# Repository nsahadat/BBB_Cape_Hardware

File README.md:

# BBB_Cape_Hardware
This cape is used to interface with wheelchair, PC, Smartphones, and Smarthomes

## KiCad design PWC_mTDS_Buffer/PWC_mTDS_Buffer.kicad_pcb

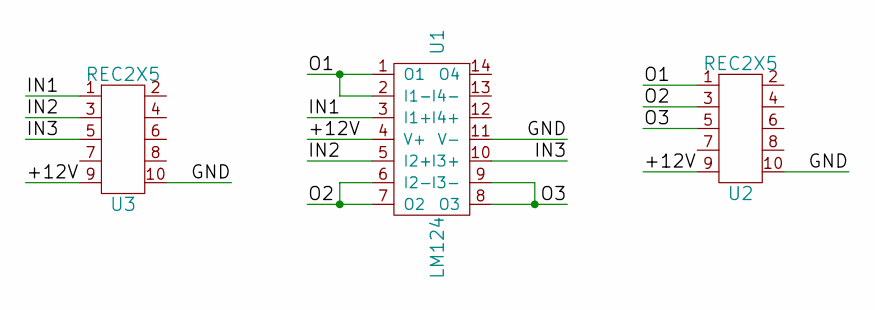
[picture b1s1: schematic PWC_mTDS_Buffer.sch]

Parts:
U1: LM124
U2: REC2X5; REC2X5_254MM
U3: REC2X5; REC2X5_127MM

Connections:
/+12V: U1.4 (V+), U2.9, U3.9
/GND: U1.11 (V-), U2.10, U3.10
/IN1: U1.3 (I1+), U3.1
/IN2: U1.5 (I2+), U3.3
/IN3: U1.10 (I3+), U3.5
/O1: U1.1 (O1), U1.2 (I1-), U2.1
/O2: U1.6 (I2-), U1.7 (O2), U2.3
/O3: U1.8 (O3), U1.9 (I3-), U2.5

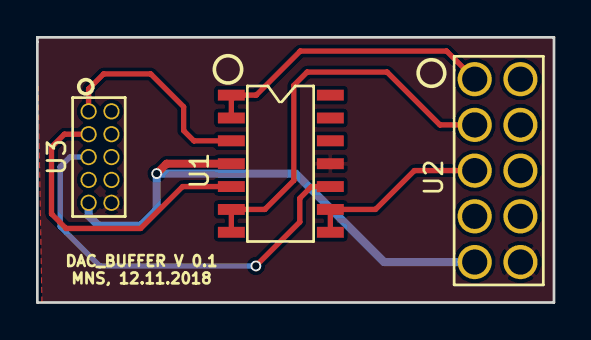
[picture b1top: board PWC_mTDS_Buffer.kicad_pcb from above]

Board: 2 copper layers, 28.7 x 14.7 mm, 3 parts (0 on the bottom side), 8 nets.

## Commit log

2019-10-13 BBB Cape design in Allegro
2019-10-13 no message
2019-10-13 Buffer to stabilize DAC output to drive the wheelchair
